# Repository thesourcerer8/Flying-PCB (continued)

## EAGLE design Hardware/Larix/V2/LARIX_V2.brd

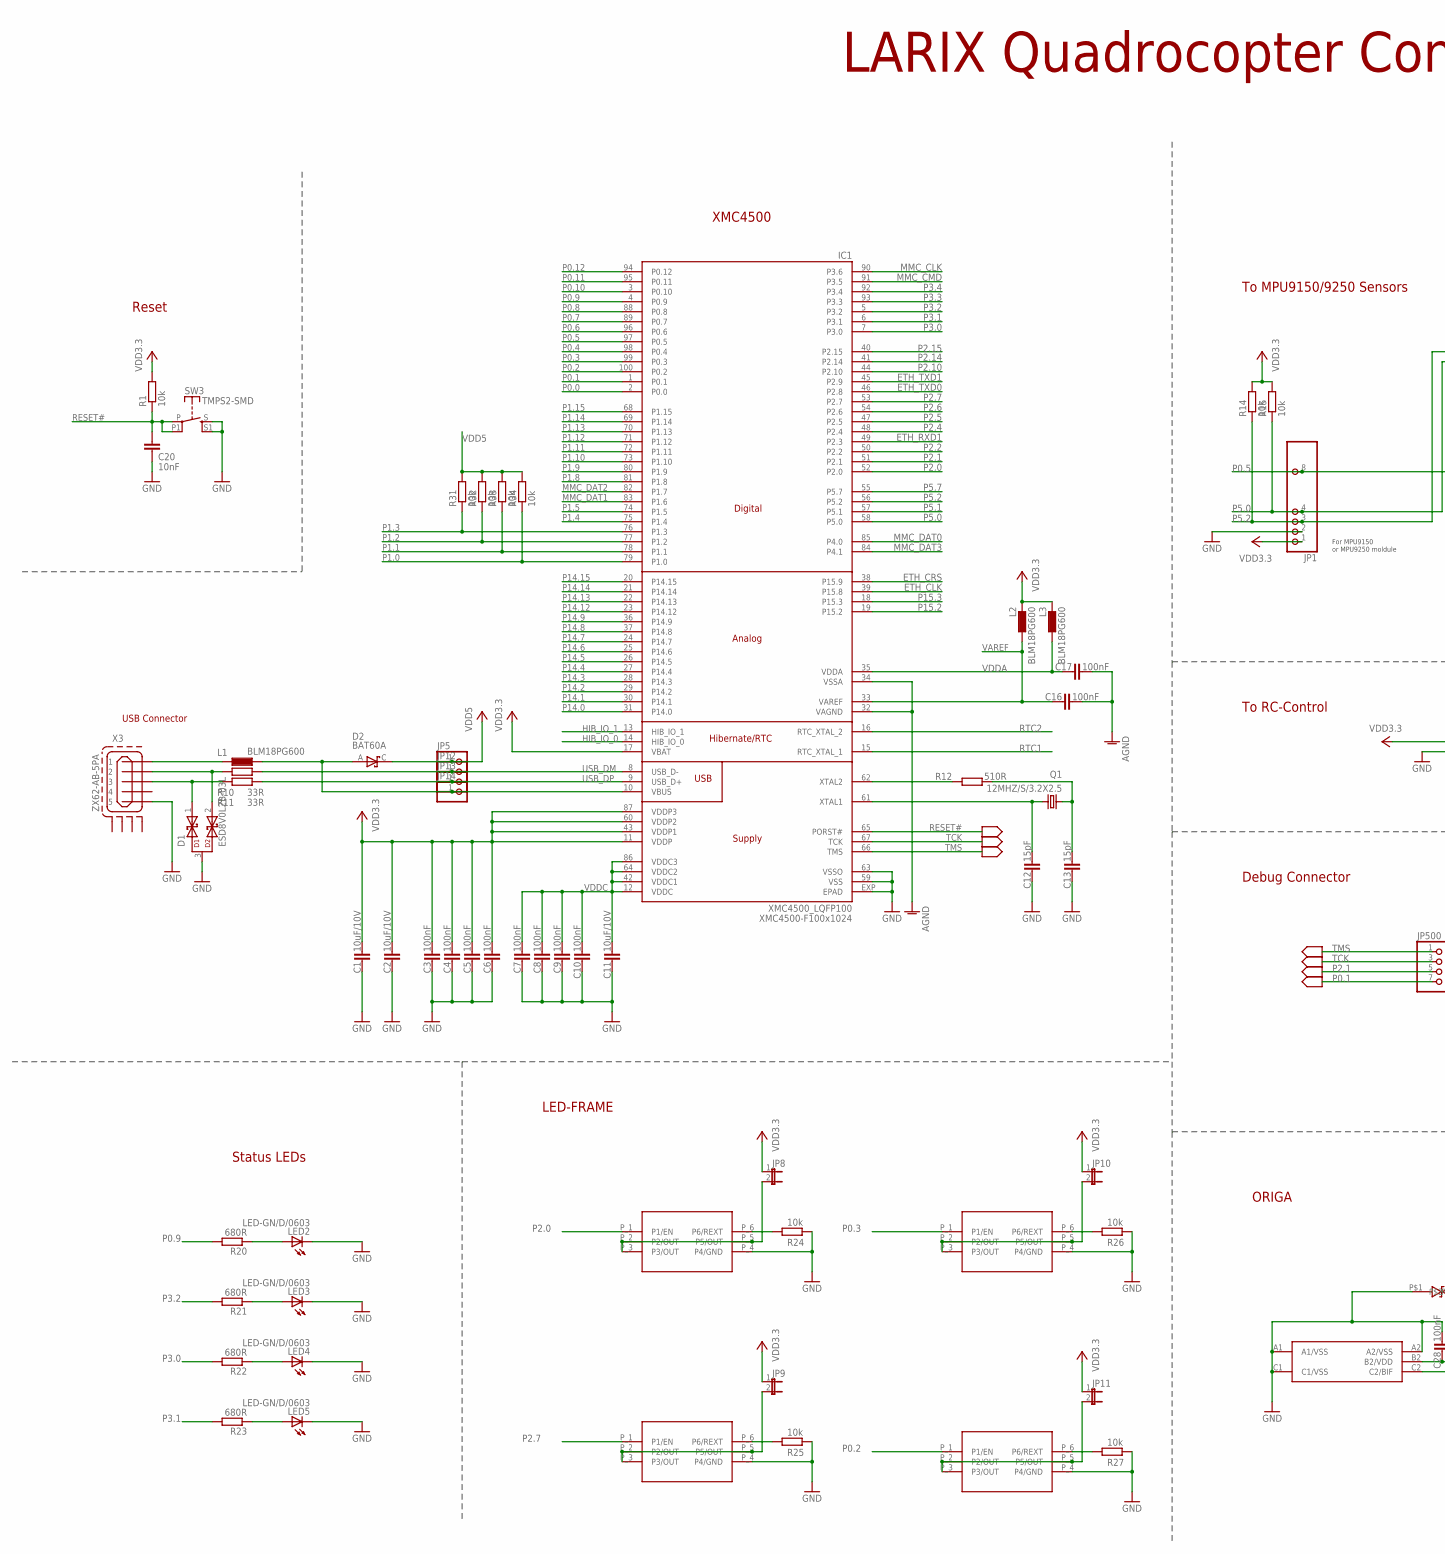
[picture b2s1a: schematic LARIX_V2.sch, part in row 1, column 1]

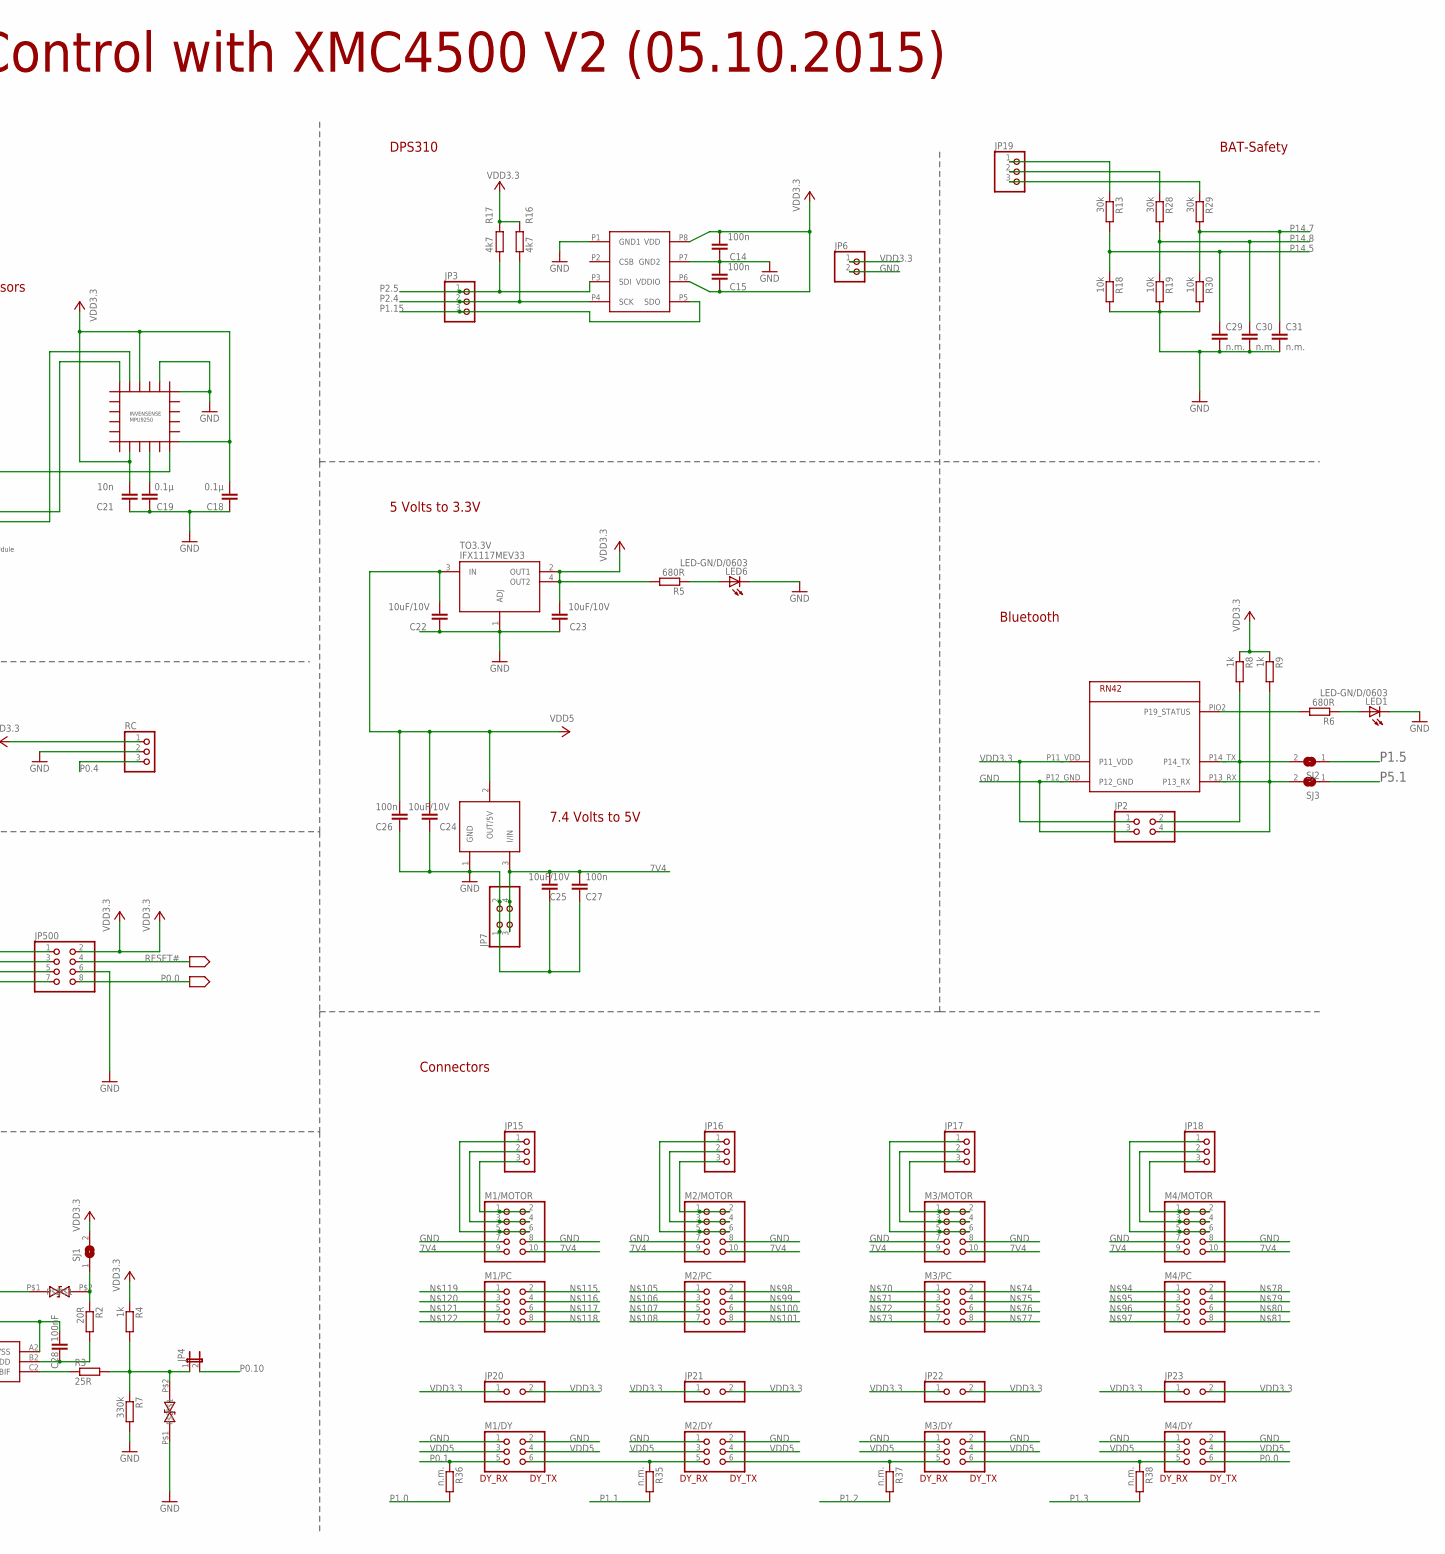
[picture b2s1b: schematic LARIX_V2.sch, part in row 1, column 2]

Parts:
C1, C2, C11, C22, C23, C24, C25: 10uF/10V; C0805K
C3, C4, C5, C6, C7, C8, C9, C10, C16, C17, C28: 100nF; C0603
C12, C13: 15pF; C0603
C14, C15, C26, C27: 100n; C0603
C18, C19: 0.1µ; C0603
C20: 10nF; C0603
C21: 10n; C0603
C29, C30, C31: n.m.; C0603
D1: ESD8V0L2B-03L; TSLP-3-1
D2: BAT60A; SOD323-R
IC1: XMC4500_LQFP100; P/PG-LQFP-100-11
IC2: INVENSENSE9250EHERBY; QFN3X3-24+
JP1: PINHD-1X10; 1X10
JP2, JP7: PINHD-2X2; 2X02
JP3, JP15, JP16, JP17, JP18, JP19: PINHD-1X3; 1X03
JP4, JP8, JP9, JP10, JP11: JP1E; JP1
JP5, JP12, JP13, JP14: PINHD-1X1; 1X01
JP6: PINHD-1X2; 1X02
JP20, JP21, JP22, JP23: PINHD-2X3; 2X03
JP500: PINHD-2X4; 2X04
L1, L2, L3: BLM18PG600; L1608
LED1, LED2, LED3, LED4, LED5, LED6: LED-GN/D/0603; CHIPLED_0603
M1/DY, M2/DY, M3/DY, M4/DY: PINHD-2X3; 2X03
M1/MOTOR, M2/MOTOR, M3/MOTOR, M4/MOTOR: PINHD-2X5; 2X05
M1/PC, M2/PC, M3/PC, M4/PC: PINHD-2X4; 2X04
Q1: 12MHZ/S/3.2X2.5; 32X25_4PAD
R1, R14, R15, R18, R19, R24, R25, R26, R27, R30, R31, R32, R33, R34: 10k; R0603
R2: 20R; R0603
R3: 25R; R0603
R4, R8, R9: 1k; R0603
R5, R6, R20, R21, R22, R23: 680R; R0603
R7: 330k; R0603
R10, R11: 33R; R0603
R12: 510R; R0603
R13, R28, R29: 30k; R0603
R16, R17: 4k7; R0603
R35, R36, R37, R38: n.m.; R0603
RC: PINHD-1X3; 1X03
SJ1, SJ2, SJ3: SJ
SW3: TMPS2-SMD; FSM2JSMA
TO3.3V: IFX1117MEV33; SOT223
U$7: TLE4284V50; INF-PG-TO252-3-1_L_1PRIMARY
U$8: DPS310DRUCKSENSOR; LGA8R125P0X4_500X300X120
U$9, U$22: ESD218-B1-02EL; TSLP-2-20
U$11: ORIGA2L; WLB-5
U$13, U$15, U$18, U$20: BCU320; SC74
U$16: BLUETOOTHRN42; ROVING-SHORT
X3: ZX62-AB-5PA; ZX62-AB-5PA_MICRO-USB

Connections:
7V4: C25.1, C27.1, JP7.3, JP7.4, M1/MOTOR.9, M1/MOTOR.10, M2/MOTOR.9, M2/MOTOR.10, M3/MOTOR.9, M3/MOTOR.10, M4/MOTOR.9, M4/MOTOR.10, U$7.3 (I/IN)
AGND: C16.2, C17.2, IC1.32 (VAGND), IC1.34 (VSSA)
BLUETOOTHLED: R6.2, U$16.PIO2 (P19_STATUS)
ETH_CLK: IC1.39 (P15.8)
ETH_CRS: IC1.38 (P15.9)
ETH_RXD1: IC1.49 (P2.3)
ETH_TXD0: IC1.46 (P2.8)
ETH_TXD1: IC1.45 (P2.9)
GND: C1.2, C2.2, C3.2, C4.2, C5.2, C6.2, C7.2, C8.2, C9.2, C10.2, C11.2, C12.2, C13.2, C14.2, C15.1, C18.1, C19.1, C20.2, C21.1, C22.2, C23.2, C24.2, C25.2, C26.2, C27.2, C28.1, C29.2, C30.2, C31.2, D1.3, IC1.59 (VSS), IC1.63 (VSSO), IC1.EXP (EPAD), IC2.18, IC2.20, JP1.2, JP2.3, JP6.2, JP7.1, JP7.2, JP500.6, LED1.C, LED2.C, LED3.C, LED4.C, LED5.C, LED6.C, M1/DY.1, M1/DY.2, M1/MOTOR.7, M1/MOTOR.8, M2/DY.1, M2/DY.2, M2/MOTOR.7, M2/MOTOR.8, M3/DY.1, M3/DY.2, M3/MOTOR.7, M3/MOTOR.8, M4/DY.1, M4/DY.2, M4/MOTOR.7, M4/MOTOR.8, R7.2, R18.2, R19.2, R24.2, R25.2, R26.2, R27.2, R30.2, RC.2, SW3.S, SW3.S1 (S), TO3.3V.1 (ADJ), U$7.1 (GND), U$8.P1 (GND1), U$8.P7 (GND2), U$9.P$1, U$11.A1 (A1/VSS), U$11.A2 (A2/VSS), U$11.C1 (C1/VSS), U$13.P_4 (P4/GND), U$15.P_4 (P4/GND), U$16.P12_GND, U$18.P_4 (P4/GND), U$20.P_4 (P4/GND), U$22.P$1, X3.5
HIB_IO_0: IC1.14 (HIB_IO_0)
HIB_IO_1: IC1.13 (HIB_IO_1)
MMC_CLK: IC1.90 (P3.6)
MMC_CMD: IC1.91 (P3.5)
MMC_DAT0: IC1.85 (P4.0)
MMC_DAT1: IC1.83 (P1.6)
MMC_DAT2: IC1.82 (P1.7)
MMC_DAT3: IC1.84 (P4.1)
unnamed: LED2.A, R20.1
unnamed: C28.2, R2.2, U$11.B2 (B2/VDD)
unnamed: LED3.A, R21.1
unnamed: IC1.62 (XTAL2), R12.1
unnamed: C13.1, Q1.3 (2), R12.2
unnamed: C12.1, IC1.61 (XTAL1), Q1.1
unnamed: JP4.1, R3.2, R4.2, R7.1, U$22.P$2
unnamed: R2.1, SJ1.1, U$9.P$2
unnamed: L1.2, X3.1
unnamed: R3.1, U$11.C2 (C2/BIF)
unnamed: D1.2, R10.1, X3.2
unnamed: JP15.1, M1/MOTOR.5, M1/MOTOR.6
unnamed: LED6.A, R5.1
unnamed: M2/DY.6, M3/DY.5, R37.1
unnamed: LED1.A, R6.1
unnamed: C19.2, IC2.10
unnamed: JP15.2, M1/MOTOR.3, M1/MOTOR.4
unnamed: LED4.A, R22.1
unnamed: D2.A, IC1.10 (VBUS), JP14.1, L1.1
unnamed: LED5.A, R23.1
unnamed: JP15.3, M1/MOTOR.1, M1/MOTOR.2
unnamed: R24.1, U$13.P_6 (P6/REXT)
unnamed: JP8.2, U$13.P_2 (P2/OUT), U$13.P_3 (P3/OUT), U$13.P_5 (P5/OUT)
unnamed: R25.1, U$15.P_6 (P6/REXT)
unnamed: JP9.2, U$15.P_2 (P2/OUT), U$15.P_3 (P3/OUT), U$15.P_5 (P5/OUT)
unnamed: R26.1, U$18.P_6 (P6/REXT)
unnamed: JP10.2, U$18.P_2 (P2/OUT), U$18.P_3 (P3/OUT), U$18.P_5 (P5/OUT)
unnamed: R27.1, U$20.P_6 (P6/REXT)
unnamed: JP11.2, U$20.P_2 (P2/OUT), U$20.P_3 (P3/OUT), U$20.P_5 (P5/OUT)
unnamed: JP16.1, M2/MOTOR.5, M2/MOTOR.6
unnamed: D1.1, R11.1, X3.3
unnamed: JP19.1, R13.1
unnamed: JP16.3, M2/MOTOR.1, M2/MOTOR.2
unnamed: JP16.2, M2/MOTOR.3, M2/MOTOR.4
unnamed: JP19.2, R28.1
unnamed: JP18.1, M4/MOTOR.5, M4/MOTOR.6
unnamed: JP19.3, R29.1
unnamed: JP18.3, M4/MOTOR.1, M4/MOTOR.2
unnamed: JP18.2, M4/MOTOR.3, M4/MOTOR.4
unnamed: JP17.1, M3/MOTOR.5, M3/MOTOR.6
unnamed: JP17.2, M3/MOTOR.3, M3/MOTOR.4
unnamed: JP17.3, M3/MOTOR.1, M3/MOTOR.2
unnamed: M3/DY.6, M4/DY.5, R38.1
unnamed: M1/DY.6, M2/DY.5, R35.1
P0.0: IC1.2 (P0.0), JP500.8, M4/DY.6
P0.1: IC1.1 (P0.1), JP500.7, M1/DY.5, R36.1
P0.2: IC1.100 (P0.2), U$20.P_1 (P1/EN)
P0.3: IC1.99 (P0.3), U$18.P_1 (P1/EN)
P0.4: IC1.98 (P0.4), RC.3
P0.5: IC1.97 (P0.5), IC2.12, JP1.8
P0.6: IC1.96 (P0.6)
P0.7: IC1.89 (P0.7)
P0.8: IC1.88 (P0.8)
P0.9: IC1.4 (P0.9), R20.2
P0.10: IC1.3 (P0.10), JP4.2
P0.11: IC1.95 (P0.11)
P0.12: IC1.94 (P0.12)
P1.0: IC1.79 (P1.0), R34.1, R36.2
P1.1: IC1.78 (P1.1), R33.1, R35.2
P1.2: IC1.77 (P1.2), R32.1, R37.2
P1.3: IC1.76 (P1.3), R31.1, R38.2
P1.4: IC1.75 (P1.4)
P1.5: IC1.74 (P1.5), SJ2.1
P1.5B: JP2.4, R9.2, SJ3.2, U$16.P13_RX
P1.8: IC1.81 (P1.8)
P1.9: IC1.80 (P1.9)
P1.10: IC1.73 (P1.10)
P1.11: IC1.72 (P1.11)
P1.12: IC1.71 (P1.12)
P1.13: IC1.70 (P1.13)
P1.14: IC1.69 (P1.14)
P1.15: IC1.68 (P1.15), JP3.3, U$8.P5 (SDO)
P2.0: IC1.52 (P2.0), U$13.P_1 (P1/EN)
P2.1: IC1.51 (P2.1), JP500.5
P2.2: IC1.50 (P2.2)
P2.4: IC1.48 (P2.4), JP3.2, R16.2, U$8.P4 (SCK)
P2.5: IC1.47 (P2.5), JP3.1, R17.2, U$8.P3 (SDI)
P2.6: IC1.54 (P2.6)
P2.7: IC1.53 (P2.7), U$15.P_1 (P1/EN)
P2.10: IC1.44 (P2.10)
P2.14: IC1.41 (P2.14)
P2.15: IC1.40 (P2.15)
P3.0: IC1.7 (P3.0), R22.2
P3.1: IC1.6 (P3.1), R23.2
P3.2: IC1.5 (P3.2), R21.2
P3.3: IC1.93 (P3.3)
P3.4: IC1.92 (P3.4)
P5.0: IC1.58 (P5.0), IC2.24, JP1.4, R15.1
P5.1: IC1.57 (P5.1), SJ3.1
P5.1B: JP2.2, R8.2, SJ2.2, U$16.P14_TX
P5.2: IC1.56 (P5.2), IC2.23, JP1.3, R14.1
P5.7: IC1.55 (P5.7)
P14.0: IC1.31 (P14.0)
P14.1: IC1.30 (P14.1)
P14.2: IC1.29 (P14.2)
P14.3: IC1.28 (P14.3)
P14.4: IC1.27 (P14.4)
P14.5: C29.1, IC1.26 (P14.5), R13.2, R18.1
P14.6: IC1.25 (P14.6)
P14.7: C31.1, IC1.24 (P14.7), R29.2, R30.1
P14.8: C30.1, IC1.37 (P14.8), R19.1, R28.2
P14.9: IC1.36 (P14.9)
P14.12: IC1.23 (P14.12)
P14.13: IC1.22 (P14.13)
P14.14: IC1.21 (P14.14)
P14.15: IC1.20 (P14.15)
P15.2: IC1.19 (P15.2)
P15.3: IC1.18 (P15.3)
RESET#: C20.1, IC1.65 (PORST#), JP500.4, R1.1, SW3.P, SW3.P1
RTC1: IC1.15 (RTC_XTAL_1)
RTC2: IC1.16 (RTC_XTAL_2)
TCK: IC1.67 (TCK), JP500.3
TMS: IC1.66 (TMS), JP500.1
USB_DM: IC1.8 (USB_D-), JP12.1, R10.2
USB_DP: IC1.9 (USB_D+), JP13.1, R11.2
VAREF: C16.1, IC1.33 (VAREF), L2.1
VDD3.3: C1.1, C2.1, C3.1, C4.1, C5.1, C6.1, C14.1, C15.2, C18.2, C21.2, C23.1, IC1.11 (VDDP), IC1.17 (VBAT), IC1.43 (VDDP1), IC1.60 (VDDP2), IC1.87 (VDDP3), IC2.8, IC2.13, IC2.22, JP1.1, JP2.1, JP6.1, JP8.1, JP9.1, JP10.1, JP11.1, JP20.1, JP20.2, JP21.1, JP21.2, JP22.1, JP22.2, JP23.1, JP23.2, JP500.2, L2.2, L3.2, R1.2, R4.1, R5.2, R8.1, R9.1, R14.2, R15.2, R16.1, R17.1, RC.1, SJ1.2, TO3.3V.2 (OUT1), TO3.3V.4 (OUT2), U$8.P6 (VDDIO), U$8.P8 (VDD), U$16.P11_VDD
VDD5: C22.1, C24.1, C26.1, D2.C, JP5.1, M1/DY.3, M1/DY.4, M2/DY.3, M2/DY.4, M3/DY.3, M3/DY.4, M4/DY.3, M4/DY.4, R31.2, R32.2, R33.2, R34.2, TO3.3V.3 (IN), U$7.2 (OUT/5V)
VDDA: C17.1, IC1.35 (VDDA), L3.1
VDDC: C7.1, C8.1, C9.1, C10.1, C11.1, IC1.12 (VDDC), IC1.42 (VDDC1), IC1.64 (VDDC2), IC1.86 (VDDC3)

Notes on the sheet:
USB Connector
Reset
LARIX Quadrocopter Control with XMC4500 V2 (05.10.2015)
XMC4500-F100x1024
To RC-Control
To MPU9150/9250 Sensors
Debug Connector
DPS310
ORIGA
Status LEDs
LED-FRAME
5 Volts to 3.3V
7.4 Volts to 5V
Connectors
Bluetooth
BAT-Safety
DY_RX
DY_TX
XMC4500
For MPU9150 or MPU9250 moldule

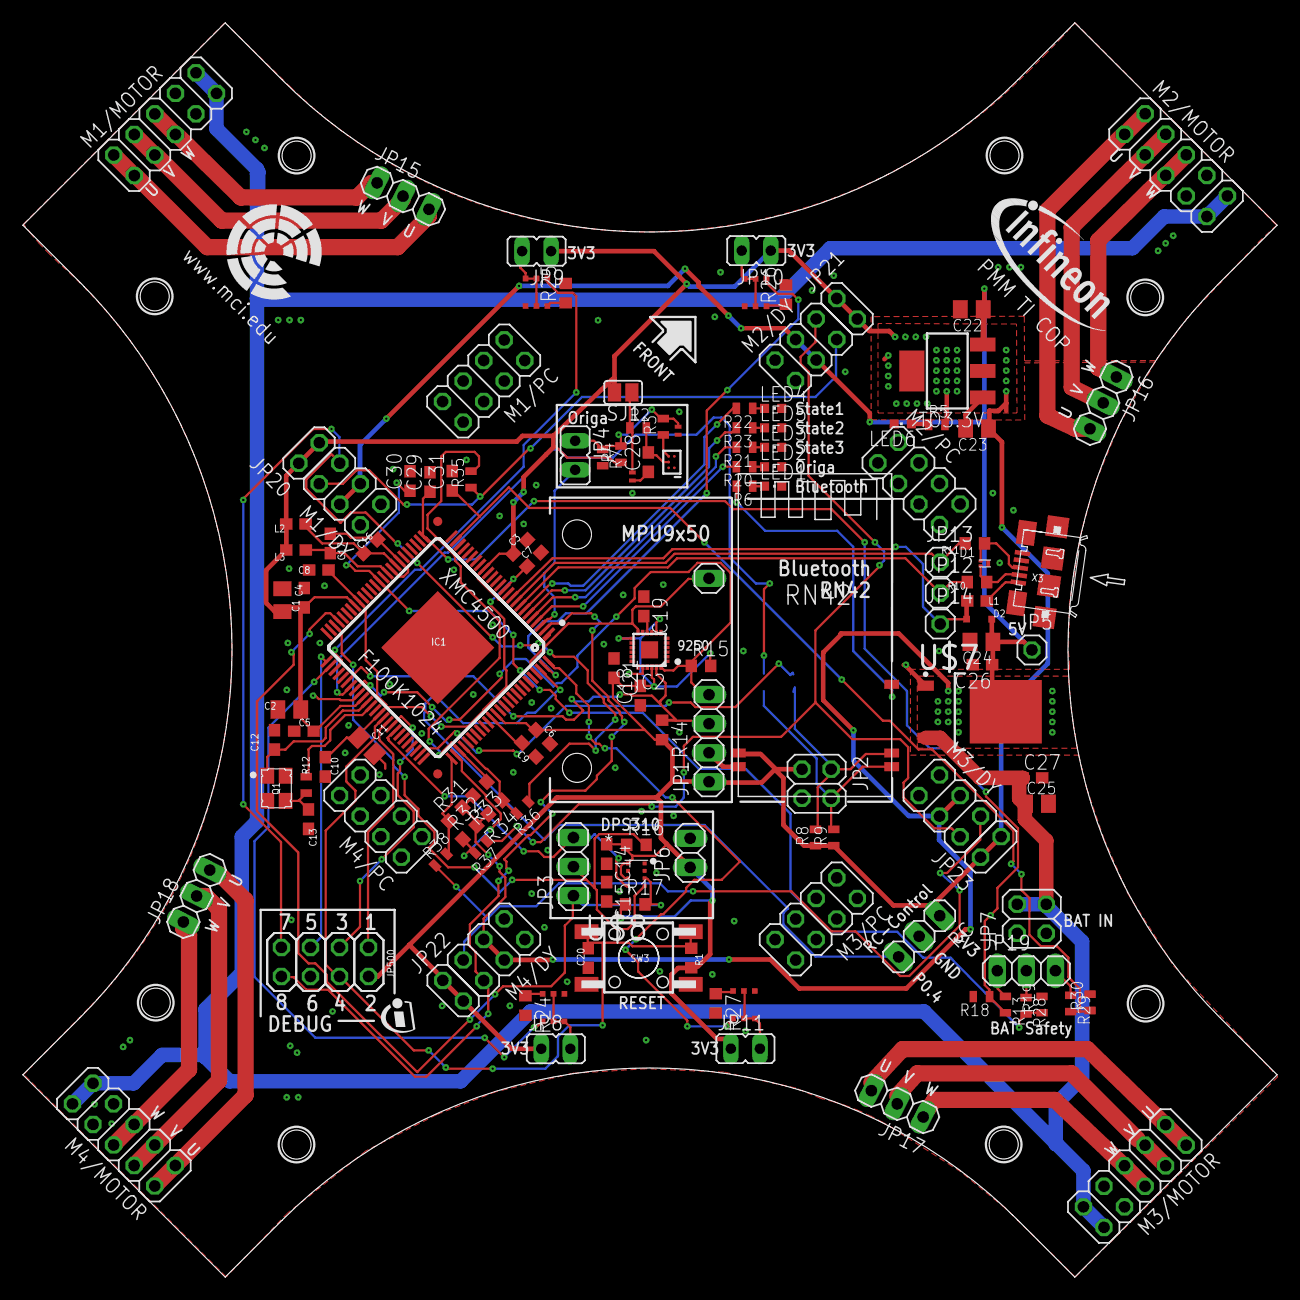
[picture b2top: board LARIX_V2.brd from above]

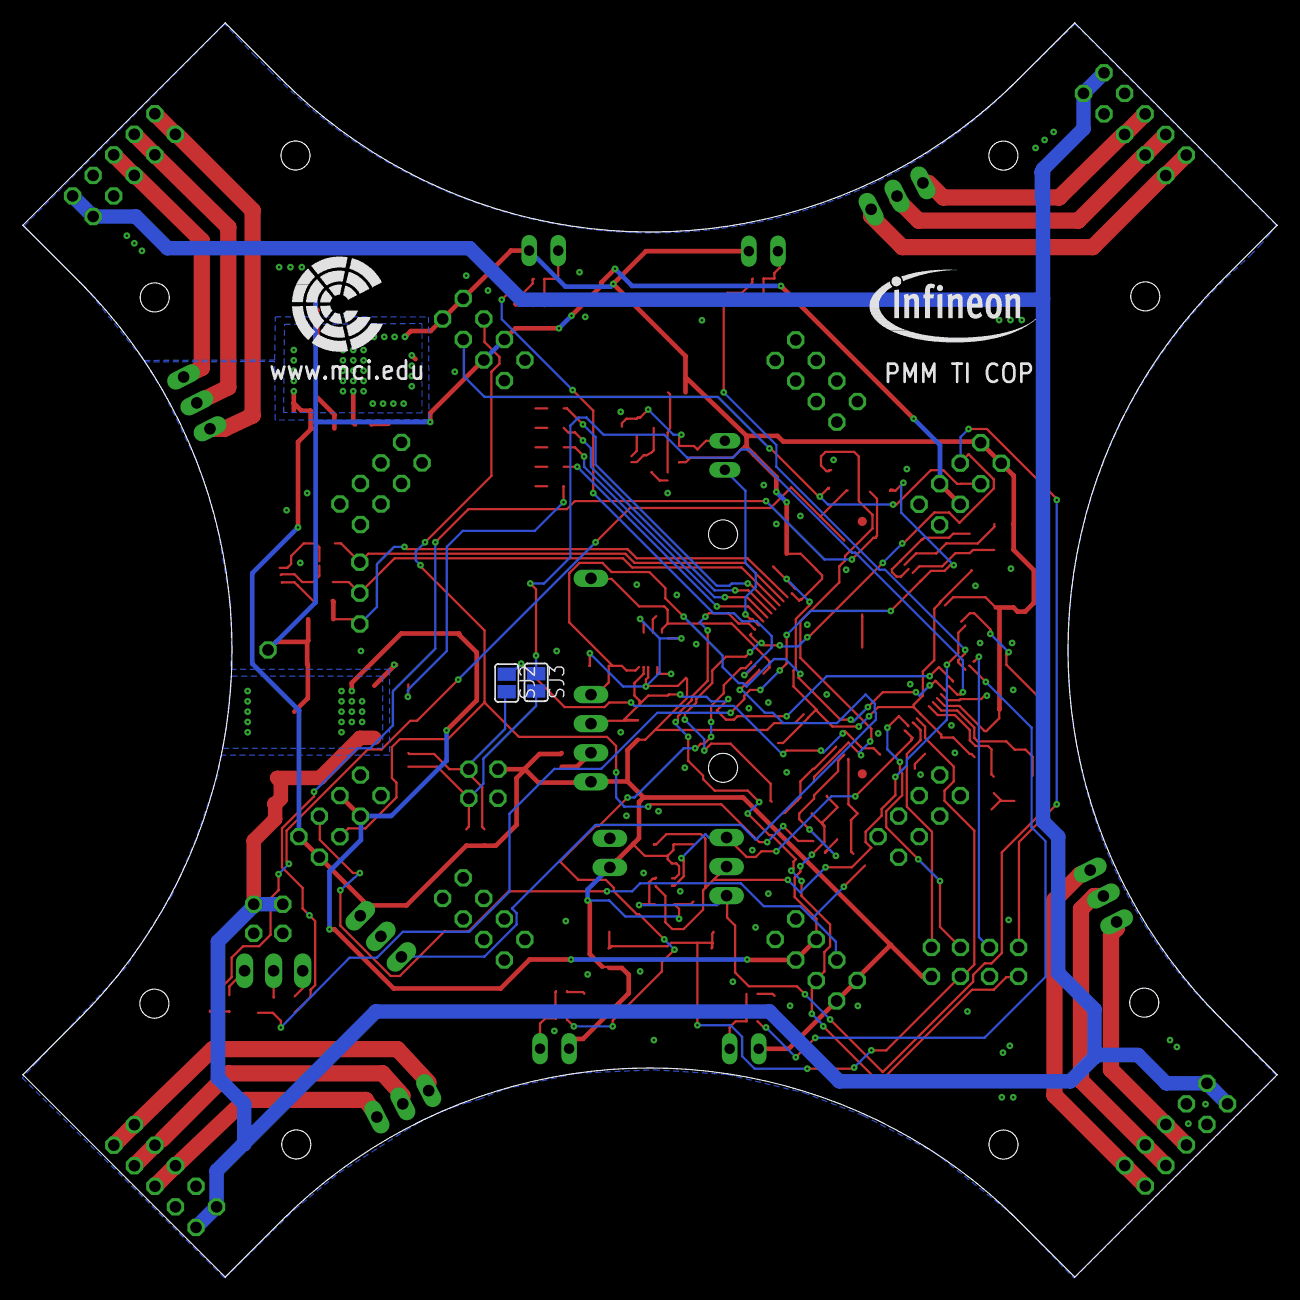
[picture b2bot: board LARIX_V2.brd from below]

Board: 2 copper layers, 109.6 x 109.6 mm, 137 parts (2 on the bottom side), 88 nets.

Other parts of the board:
U$12: INFINEON_ICON_3-SILK

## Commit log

2015-11-24 Hardware
2015-11-30 simulation
2015-11-30 constants added
2015-11-30 changed
2016-02-05 added folder Software
2016-02-05 added Software archive
2016-02-05 deleted files
2016-02-05 added pinus
2016-02-05 added folder Hardware
2016-02-11 added flightframe
2016-02-11 added Software folder
2016-04-14 Widefield
2016-04-14 LARIX
2016-04-14 LARIX-PINUS
2016-06-01 Unpacked .zip file
2016-06-16 Rename Hardware/Foot_Clip.stp to Hardware/Flightframe/Foot_Clip.stp
2016-06-16 Rename Hardware/Larix_Frame_v7.dxf to Hardware/Flightframe/Larix_Frame_v7.dxf
2016-06-16 Rename Hardware/Larix_Frame_v7.stp to Hardware/Flightframe/Larix_Frame_v7.stp
2016-06-17 Adding Bluetooth protocol client
2016-06-25 Ported the Widefield software to Linux/GCC for simulation
2016-06-25 Adding motor test code
2016-06-29 Spektrum DX6i -> Arduino -> ardu2sim.pl -> Simulation
2016-06-29 New copter simulator version
    Rotation damping - now it is easier to control
    Interface to Widefield Software and Spektrum DX6i over UDP
2016-07-16 Added missing channels
2016-07-17 Ported to Linux
